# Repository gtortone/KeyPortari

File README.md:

# 🕹️⌨️ The KeyPortari a 2600/7800 Keyboard Interface

This project enables the connection of a PS/2 keyboard (or a USB keyboard that supports the PS/2 protocol) to the Atari 2600 or 7800 console. The ATmega328P processes keystrokes and controls the joystick inputs of the Atari 2600 accordingly.

## ✨ Features
- **PS/2 Keyboard Support**: Supports various keyboard layouts (DE, US, FR).
- **Direct ASCII Conversion**: Translates keystrokes into Atari 2600-compatible signals.
- **Configurable Keymaps**: Customizable key assignments for Atari 2600 control.
- **Efficient GPIO Usage**: Utilizes an 8-bit port for direct control.
- **Configurable DIP Switches**: 4-bit resistor-ladder circuit for easy configuration.

## 🔌 Hardware Requirements
- **ATmega328P 5V 16Mhz (Arduino-compatible)**
- **PS/2 Keyboard (or USB Keyboard that supports the PS/2 protocol)**
- **Resistors for Resistor-Ladder (10kΩ, 20kΩ, 40kΩ, 80kΩ, 100kΩ Pull-up)**
- **2x Quad analog switch (74HC4066)**
- **Joystick port connection for the Atari 2600**

## 🛠️ Sponsored by JLCPCB
PCB manufacturing for this project was kindly sponsored by [JLCPCB](https://jlcpcb.com/?from=KEYPORTARI) – a leading PCB prototype service.
For the first prototype run, [JLCPCB](https://jlcpcb.com/?from=KEYPORTARI) generously provided 15 SMD assembled test boards, helping to accelerate early hardware development.

If you’re a developer or hardware tinkerer and would like to experiment with the interface or contribute your own ideas, feel free to reach out to me via [AtariAge](https://forums.atariage.com/topic/380359-the-keyportari-a-keyboard-interface-for-the-atari-26007800/page/4/#findComment-5660044) – I’d be happy to provide a board to support your work.

## 🧪 Breadboard Setup (one joystick forwarded)

## ⚙️ Installation & Setup
1. **Upload code to ATmega328P** (via Arduino IDE or AVRDUDE).
2. **Connect PS/2 keyboard** to the corresponding pins.
3. **Set DIP switches** for the desired configuration.
4. **Connect to the Atari 2600 joystick port**.

## 🎮 Usage
- Each keystroke on the PS/2 keyboard is translated into joystick controls for the Atari 2600.
- Modifier keys like `Shift`, `Ctrl`, and `Alt` influence the key output (e.g., uppercase/lowercase characters).
- DIP switches can be used to activate different keyboard layout (US,DE,FR) configurations.

## 🐞 Known Issues & Solutions

## 🙏 Credits
- Project discussion: [AtariAge Forum](https://forums.atariage.com/topic/380359-keyboard-interface-for-the-atari-2600/)
- Open-source libraries: PS/2 Keyboard Library (modified for this project)
- Steve Guidi's ["Basic Programming" protocol](https://github.com/SteveGuidi/video-companion-media/tree/main/2021.06.09%20-%20Atari%202600%20Keyboard)

## 📄 License
- Firmware is licensed under the [MIT License](LICENSE)
- Hardware designs (schematics, PCB) are under the [CERN Open Hardware Licence v2.0 - Permissive](LICENSE-HARDWARE)

---
If you have any questions or suggestions, feel free to open an issue on GitHub! 🎮

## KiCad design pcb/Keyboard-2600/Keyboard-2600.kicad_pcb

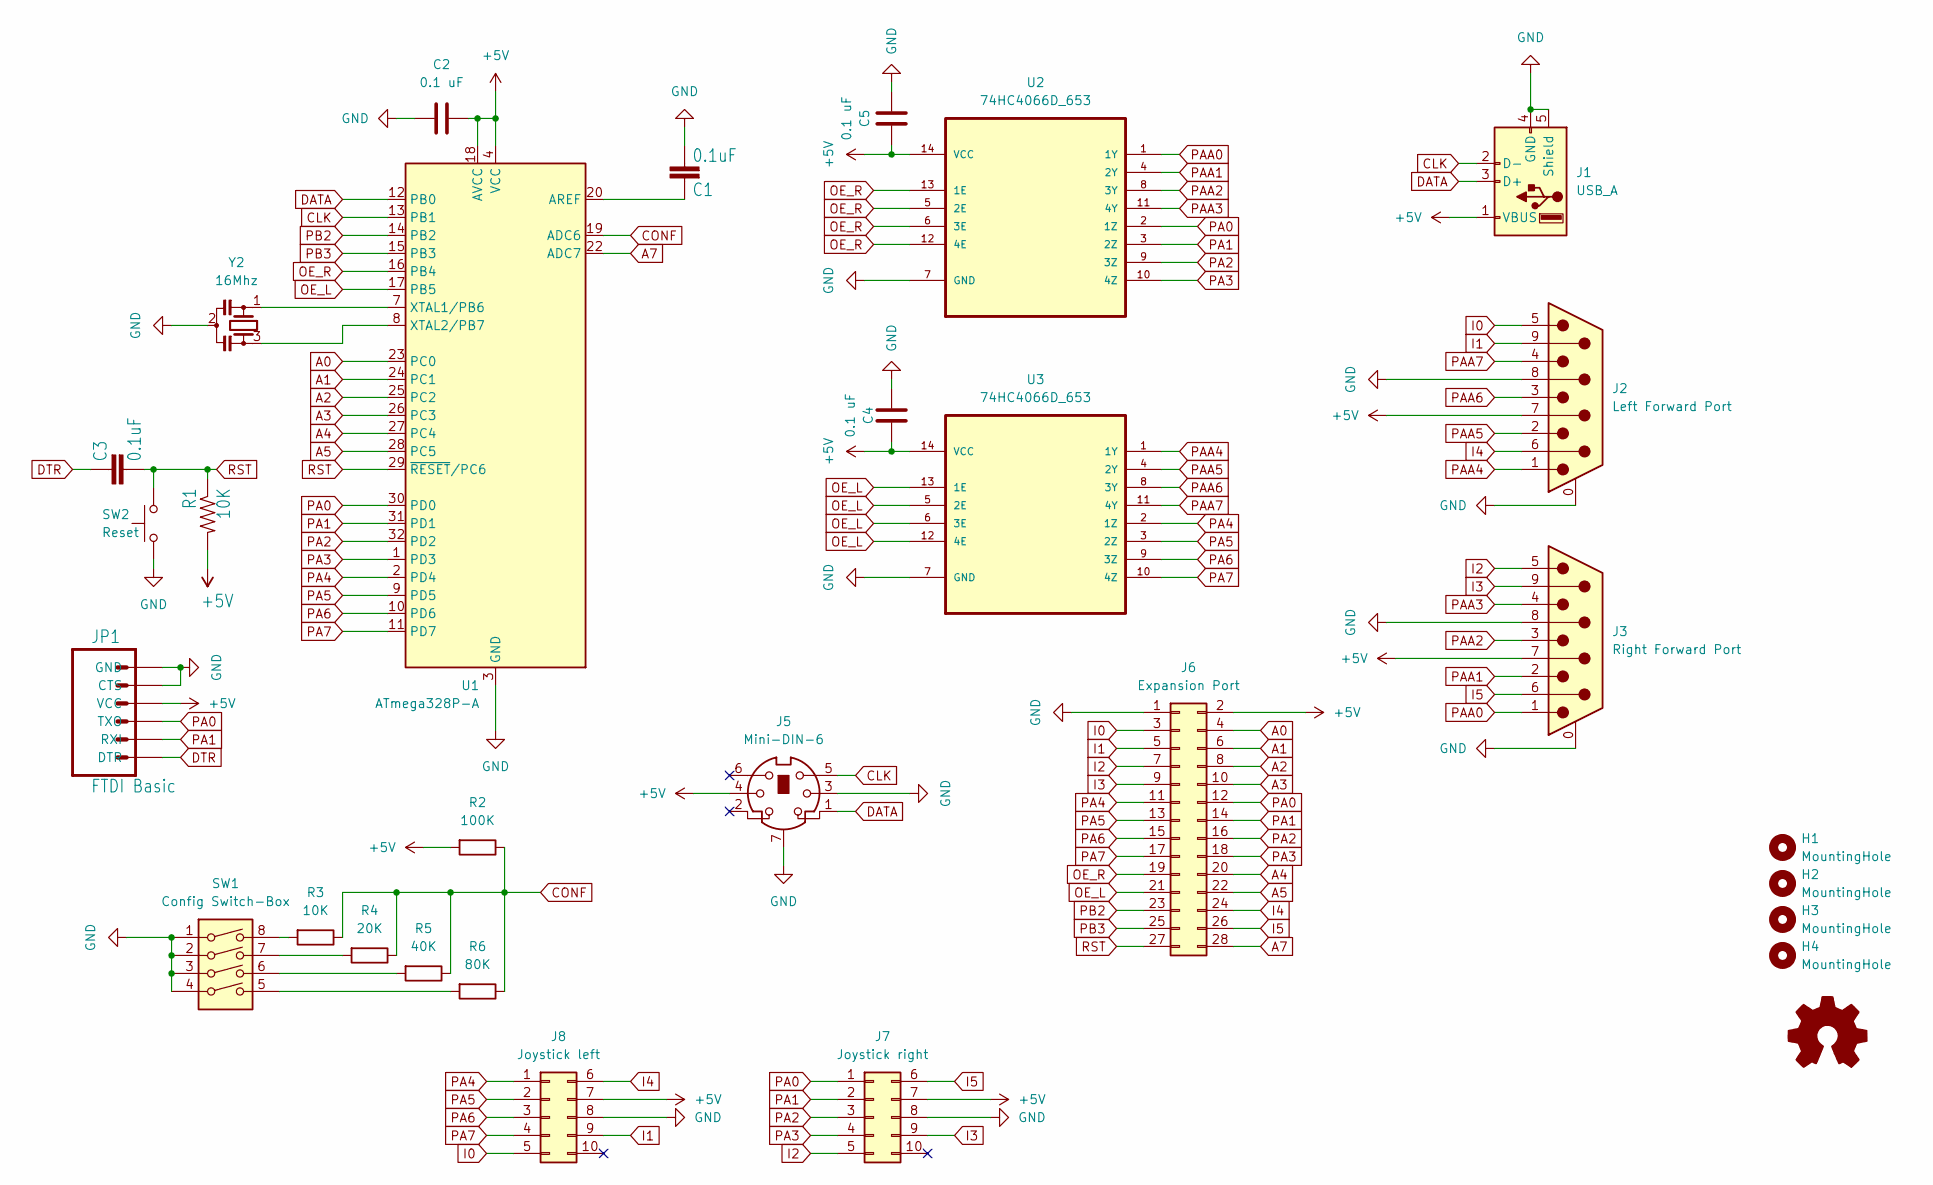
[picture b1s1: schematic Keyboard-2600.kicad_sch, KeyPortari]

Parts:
C1, C3: 0.1uF; C_0402_1005Metric
C2, C4, C5: 0.1 uF; C_0402_1005Metric
H1, H2, H3, H4: MountingHole; MountingHole_3mm
J1: USB_A; USB_A_Molex_67643_Horizontal
J2: Left Forward Port; DSUB-9_Male_Horizontal_P2.77x2.84mm_EdgePinOffset4.94mm_Hou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
J3: Right Forward Port; DSUB-9_Male_Horizontal_P2.77x2.84mm_EdgePinOffset4.94mm_Hou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
J5: Mini-DIN-6; Connector_Mini-DIN_Female_6Pin_2rows
J6: Expansion Port; PinHeader_2x14_P2.54mm_Vertical_KeyPortari_Expansion-Port
J7: Joystick right; PinHeader_2x05_P2.54mm_Vertical
J8: Joystick left; PinHeader_2x05_P2.54mm_Vertical
JP1: FTDI Basic; PinHeader_1x06_P2.54mm_Horizontal
R1, R3: 10K; R_0402_1005Metric
R2: 100K; R_0402_1005Metric
R4: 20K; R_0402_1005Metric
R5: 40K; R_0603_1608Metric
R6: 80K; R_0603_1608Metric
SW1: Config Switch-Box; SW_DIP_SPSTx04_Piano_10.8x11.72mm_W7.62mm_P2.54mm
SW2: Reset; SW_Push_1P1T_NO_CK_KMR2
U1: ATmega328P-A; TQFP-32_7x7mm_P0.8mm
U2, U3: 74HC4066D_653; SOIC-14_3.9x8.7mm_P1.27mm; MPN 74HC4066D,653
Y2: 16Mhz; Resonator_SMD_Murata_CSTxExxV-3Pin_3.0x1.1mm

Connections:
+5V: C2.2, C4.2, C5.2, J1.1 (VBUS), J2.7, J3.7, J5.4, J6.2, J7.7, J8.7, JP1.4 (VCC), R1.2, R2.2, U1.4 (VCC), U1.6 (VCC), U1.18 (AVCC), U2.14 (VCC), U3.14 (VCC)
A0: J6.4, U1.23 (PC0)
A1: J6.6, U1.24 (PC1)
A2: J6.8, U1.25 (PC2)
A3: J6.10, U1.26 (PC3)
A4: J6.20, U1.27 (PC4)
A5: J6.22, U1.28 (PC5)
A7: J6.28, U1.22 (ADC7)
CLK: J1.2 (D-), J5.5, U1.13 (PB1)
CONF: R2.1, R3.1, R4.1, R5.1, R6.1, U1.19 (ADC6)
DATA: J1.3 (D+), J5.1, U1.12 (PB0)
DTR: C3.2, JP1.1 (DTR)
GND: C1.1, C2.1, C4.1, C5.1, J1.4 (GND), J1.5 (Shield), J2.0 (PAD), J2.8, J3.0 (PAD), J3.8, J5.3, J5.7, J6.1, J7.8, J8.8, JP1.5 (CTS), JP1.6 (GND), SW1.1, SW1.2, SW1.3, SW1.4, SW2.1, U1.3 (GND), U1.5 (GND), U1.21 (GND), U2.7 (GND), U3.7 (GND), Y2.2
I0: J2.5, J6.3, J8.5
I1: J2.9, J6.5, J8.9
I2: J3.5, J6.7, J7.5
I3: J3.9, J6.9, J7.9
I4: J2.6, J6.24, J8.6
I5: J3.6, J6.26, J7.6
unnamed: R3.2, SW1.8
unnamed: R4.2, SW1.7
unnamed: R5.2, SW1.6
unnamed: R6.2, SW1.5
unnamed: C1.2, U1.20 (AREF)
unnamed: U1.7 (XTAL1/PB6), Y2.1
unnamed: U1.8 (XTAL2/PB7), Y2.3
OE_L: J6.21, U1.17 (PB5), U3.5 (2E), U3.6 (3E), U3.12 (4E), U3.13 (1E)
OE_R: J6.19, U1.16 (PB4), U2.5 (2E), U2.6 (3E), U2.12 (4E), U2.13 (1E)
PA0: J6.12, J7.1, JP1.3 (TXO), U1.30 (PD0), U2.2 (1Z)
PA1: J6.14, J7.2, JP1.2 (RXI), U1.31 (PD1), U2.3 (2Z)
PA2: J6.16, J7.3, U1.32 (PD2), U2.9 (3Z)
PA3: J6.18, J7.4, U1.1 (PD3), U2.10 (4Z)
PA4: J6.11, J8.1, U1.2 (PD4), U3.2 (1Z)
PA5: J6.13, J8.2, U1.9 (PD5), U3.3 (2Z)
PA6: J6.15, J8.3, U1.10 (PD6), U3.9 (3Z)
PA7: J6.17, J8.4, U1.11 (PD7), U3.10 (4Z)
PAA0: J3.1, U2.1 (1Y)
PAA1: J3.2, U2.4 (2Y)
PAA2: J3.3, U2.8 (3Y)
PAA3: J3.4, U2.11 (4Y)
PAA4: J2.1, U3.1 (1Y)
PAA5: J2.2, U3.4 (2Y)
PAA6: J2.3, U3.8 (3Y)
PAA7: J2.4, U3.11 (4Y)
PB2: J6.23, U1.14 (PB2)
PB3: J6.25, U1.15 (PB3)
RST: C3.1, J6.27, R1.1, SW2.2, U1.29 (~RESET/PC6)

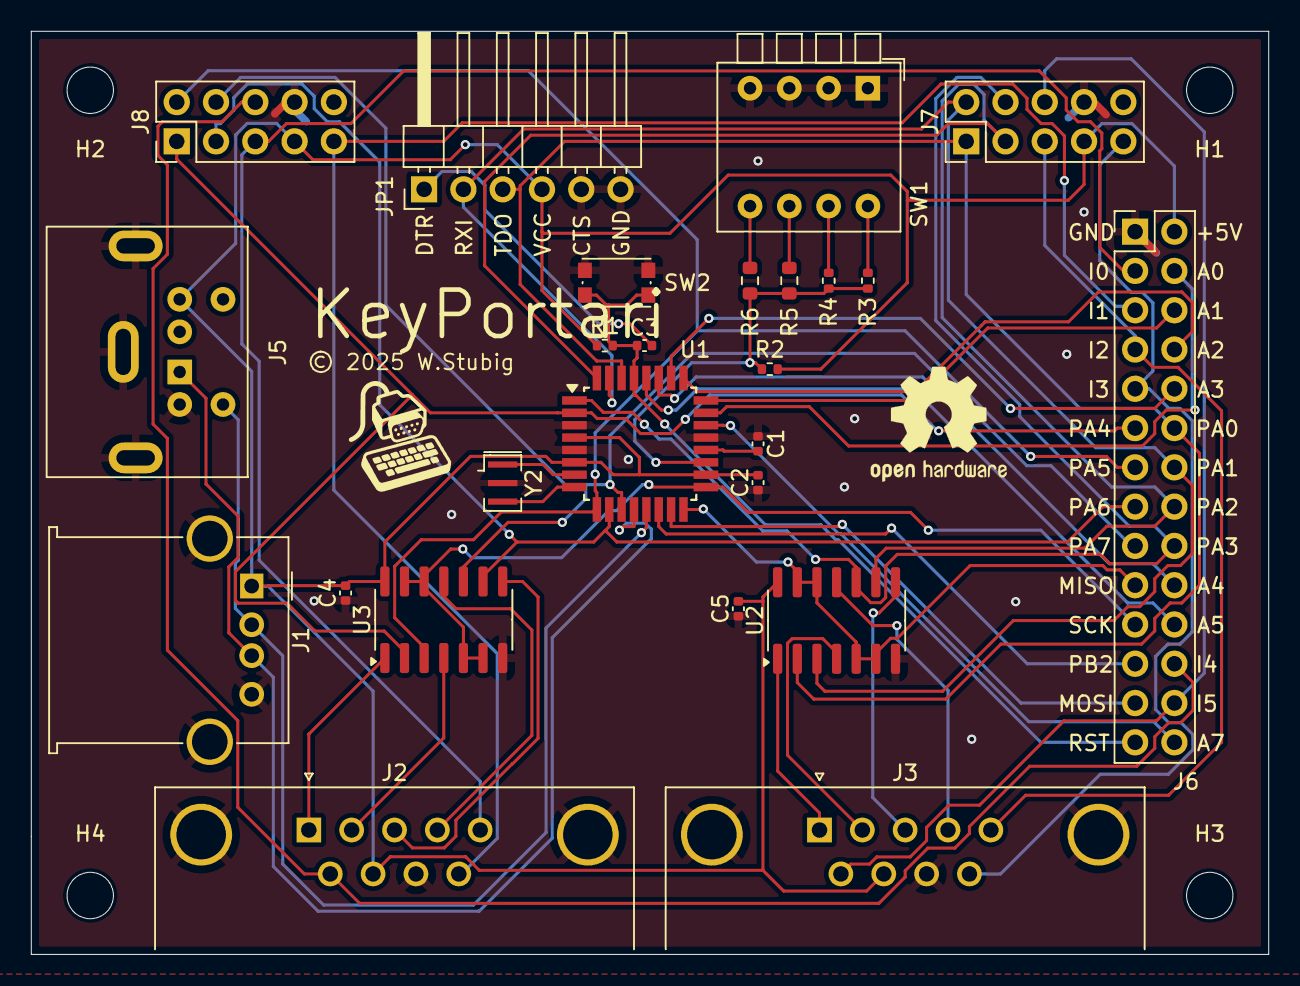
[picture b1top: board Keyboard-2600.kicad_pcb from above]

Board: 2 copper layers, 80.0 x 59.7 mm, 29 parts (0 on the bottom side), 47 nets.

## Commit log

2025-03-09 First steps with serial debugging
2025-03-28 Just pushing current state before cleanup
2025-03-29 firmware v0.0.1
2025-03-29 Add gitignore
2025-03-29 Rename Project
2025-03-29 add more ignore
2025-03-29 NTSC and PAL colors for bB ROM
2025-03-29 Font for 24 char display
2025-03-29 Add keycodes maping spreadsheet
2025-03-29 24 char display demo ROM
2025-03-30 Breadboard image
2025-03-30 Add USB host connector to breadboard
2025-03-30 add cursor movement by joystick or arrow keys
2025-04-08 New protocol and charset structure
2025-04-10 New breadboard image for 75HC5066
2025-04-10 Global header file
2025-04-13 Protocol to disable the keyboard interface
2025-04-19 Schematics and PCB layout. KiCAD 8.0
2025-04-25 rename project to KeyPortari
2025-05-10 Cleanup, keycodes for F1-F6,F10,F11
2025-05-10 Add protocol setup. And CM, BP protocol
2025-05-10 make keyboard_action a global
2025-05-10 New Charsets
2025-05-10 Add setup() to char24 protocol
2025-05-10 Add setup() to none protocol
2025-05-10 WIP state of CompuMate and BasicProgramming protocol
2025-05-10 Test board WIP state.
2025-05-10 Custom parts
2025-05-11 Create LICENSE for Software
2025-05-11 Create LICENSE-HARDWARE
2025-05-11 Update license information
2025-05-11 Add links to license
2025-05-11 Add JLCPCB sponsoring, Icons, Steve Guidi credit
2025-05-26 Fix DIP-Switch mapping
2025-06-01 Fix PROGMEM, Move enabling of 4066 to protocols
2025-06-01 Move enabling of 4066 to protocols
2025-06-02 re-routing
2025-06-16 source code refactory

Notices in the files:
pcb/Keyboard-2600/Keyboard-2600.kicad_pcb:
© 2025 W.Stubig
